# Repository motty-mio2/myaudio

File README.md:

# デスク埋込型 スマート・オーディオセレクター＆コントローラー (MyAudio)

本リポジトリは、[SPEC.md](SPEC.md) に基づいて完全設計された「デスク埋込型 スマート・オーディオセレクター＆コントローラー」のKiCad設計データ一式および製造・組立ドキュメントです。

---

## 1. プロジェクト概要

- **設計コンセプト**: 
  - 手元のデスク天板に埋め込む小型操作部（**サテライト基板**）
  - デスク天板裏に配置し、音響信号経路を最短化する主基板（**メイン基板**）
  - 両基板を市販の **LANケーブル（RJ45 Cat6）1本** で接続するスマートセパレート構成
- **手作業組立（DIY手はんだ）への最適化**:
  - すべての受動部品および主要ICに **THT（スルーホール / DIP）部品** を採用。
  - プロ用リレー・コネクタ・マイコン部も含め、一般的なはんだごて（30W〜40W程度）で失敗なく組み立て可能。
- **高音質アナログ・デジタル完全分離設計**:
  - PT2258（I2C 電子ボリュームIC）のアナロググランド（AGND）とデジタルグランド（DGND）を独立プレーン化し、1点（NetTie）のみで結合。
  - 音声信号のリレー切り替えには、高信頼性金クラッド銀接点シグナルリレー（パナソニック TQ2-5V）を採用。
- **設計品質（完全検証済み）**:
  - サテライト基板: **ERC 0件、DRC 0件、未配線 0件**
  - メイン基板: **ERC 0件、DRC 0件、未配線 0件**

---

## 2. ディレクトリ構成

```
.
├── SPEC.md                             # プロジェクト詳細要件書
├── README.md                           # 本ドキュメント
├── BOM.md                              # 部品表・調達ガイド
├── main_board-drc.rpt                  # メイン基板 DRCレポート (違反0件)
├── main_board-erc.rpt                  # メイン基板 ERCレポート (違反0件)
├── satellite-drc.rpt                   # サテライト基板 DRCレポート (違反0件)
├── satellite-erc.rpt                   # サテライト基板 ERCレポート (違反0件)
└── pcb/
    ├── generate_main_board_pcb.py      # メイン基板PCB自動配置・配線エンジン
    ├── generate_satellite_pcb.py       # サテライト基板PCB自動配置・配線エンジン
    ├── satellite/                      # サテライト操作部基板 (60mm x 45mm)
    │   ├── satellite.kicad_sch         # 回路図
    │   ├── satellite.kicad_pcb         # PCBアートワーク
    │   ├── satellite.pdf               # 回路図PDF
    │   ├── satellite_3d.png            # 3Dレンダリングプレビュー
    │   └── gerber/                     # 基板製造用ガーバー＆ドリルデータ
    └── main_board/                     # メイン音響・制御基板 (100mm x 65mm)
        ├── main_board.kicad_sch        # 回路図
        ├── main_board.kicad_pcb        # PCBアートワーク
        ├── main_board.pdf              # 回路図PDF
        ├── main_board_pcb.pdf          # PCBレイアウトPDF
        ├── main_board_3d.png           # 3Dレンダリングプレビュー
        └── gerber/                     # 基板製造用ガーバー＆ドリルデータ
```

---

## 3. 基板仕様およびレイアウト

### 3.1 サテライト基板 (`pcb/satellite/`)
- **基板外形**: 60.0 mm × 45.0 mm（角丸 R=2.0mm）
- **レイヤー構成**: 2層 (FR-4, 1.6mm厚, 1oz銅箔)
- **前面操作部配置**:
  - 左側: 0.96インチ I2C OLED (SSD1306, 128×64)
  - 中央上: 出力切替用トグルスイッチ (SPDT ON-ON)
  - 中央下: インジケータLED × 2（SPK緑 / HP青、φ3mm）
  - 右側: クリック付きロータリーエンコーダ（音量調整 & プッシュでMute）
- **背面接続部**: RJ45モジュラージャック（Cat6 LANケーブル直結）
- **製造データ**: `pcb/satellite/gerber/` 配下に標準2層ガーバー・NCドリル完備（JLCPCB / PCBWay / Elecrow等にZIP圧縮してそのまま入稿可能）。

### 3.2 メイン基板 (`pcb/main_board/`)
- **基板外形**: 100.0 mm × 65.0 mm（角丸 R=3.0mm、M3取付穴×4）
- **レイヤー構成**: 2層 (FR-4, 1.6mm厚, 1oz銅箔)
- **配置・ゾーン構成**:
  - **北側（アナログ領域）**: 
    - 3.5mmステレオジャック×3（LINE IN、SPK OUT、HP OUT）
    - PT2258 電子ボリューム部（DCカット音響コンデンサ C1〜C4）
    - 高精度 B.Cu アナロググランド（AGND）ベタプレーン
  - **中央**: 
    - 信号切替用 高信頼性シグナルリレー（パナソニック TQ2-5V）
    - 1点結合用ネットタイ（NT1）
    - LCノイズ低減電源フィルタ（L1 10uH + C6 100uF + C7 0.1uF）
  - **南側（デジタル領域）**:
    - Seeed Studio XIAO ESP32-C6 マイコンソケット
    - サテライト通信用 RJ45コネクタ
    - B.Cu デジタルグランド（DGND）ベタプレーン
- **製造データ**: `pcb/main_board/gerber/` 配下に完全な製造ガーバー・NCドリル完備。

---

## 4. RJ45 (Cat6 LANケーブル) ピンアサイン

サテライト基板とメイン基板間は、ストレート結線の Cat6 LANケーブル 1本で結線されます。ツイストペアの特性を活かし、信号間クロストークを最小化しています。

| RJ45 Pin | 芯線ペア (T568B) | 信号名 | 電圧レベル | 信号機能 |
|:---:|:---|:---|:---:|:---|
| **1** | 白橙 (ペア2) | **DGND** | 0V | システム共通デジタルグランド |
| **2** | 橙 (ペア2) | **+3V3** | 3.3V | サテライト電源 (XIAO 3.3Vレギュレータより供給) |
| **3** | 白緑 (ペア3) | **ENC_A** | 3.3V/0V | エンコーダ A相パルス (内蔵プルアップ) |
| **4** | 青 (ペア1) | **ENC_B** | 3.3V/0V | エンコーダ B相パルス (内蔵プルアップ) |
| **5** | 白青 (ペア1) | **ENC_SW** | 3.3V/0V | エンコーダ プッシュスイッチ (Mute用) |
| **6** | 緑 (ペア3) | **TOGGLE_SW**| 3.3V/0V | トグルスイッチ状態読取 |
| **7** | 白茶 (ペア4) | **LED_SPK** | 3.3V/0V | スピーカー選択LEDドライブ |
| **8** | 茶 (ペア4) | **LED_HP** | 3.3V/0V | ヘッドホン選択LEDドライブ |

> [!NOTE]
> I2Cバス (SDA / SCL) はメイン基板内で XIAO と PT2258 を接続しており、サテライト基板へは OLED 用として配線されています。長距離引き回しでも安定して動作するよう、メイン基板上に 4.7kΩ のプルアップ抵抗（R1, R2）を実装しています。

---

## 5. ファームウェア実装方針 (XIAO ESP32-C6)

### 5.1 ピンアサイン定義
- `GPIO0`: PT2258 SDA / OLED SDA
- `GPIO1`: PT2258 SCL / OLED SCL
- `GPIO2`: ENC_A (内部プルアップ、GPIO割り込み)
- `GPIO3`: ENC_B (内部プルアップ、GPIO割り込み)
- `GPIO4`: ENC_SW (内部プルアップ、チャタリング防止)
- `GPIO16`: TOGGLE_SW (内部プルアップ)
- `GPIO17`: LED_SPK (HIGHで点灯)
- `GPIO18`: LED_HP (HIGHで点灯)
- `GPIO19`: RELAY_CTRL (HIGHでリレーON = HP出力、LOWでSPK出力)

### 5.2 制御ロジック
1. **音量制御 (PT2258)**:
   - アドレス: `0x88` (ADDR接地時)
   - エンコーダ回転に応じて 0〜-79 dB（1dBステップ）で減衰量を I2C 送信。
   - Mute 時は PT2258 の Mute コマンド (`0xF9`) を発行し、OLED に「MUTE」を表示。
2. **出力切替 (ポップノイズ防止シーケンス)**:
   - トグルスイッチ操作検知時：
     1. PT2258 をソフトウェア Mute に設定
     2. 20ms ウェイト（音声信号遮断を待機）
     3. リレー（GPIO19）を反転駆動
     4. 30ms ウェイト（リレー接点のバウンス収束を待機）
     5. PT2258 の Mute を解除
   - これにより、スピーカーやヘッドホンから一切の切替ポップノイズが発生しません。
3. **USB 音量同期 & WebUI**:
   - ESP32-C6 の Native USB により、PCと接続時に USB HID Consumer Control（Volume Up/Down/Mute）としても連動可能。
   - ESP-NOW / Wi-Fi を用いて、将来的なホームオートメーション連携も拡張可能。

---

## 6. 品質検査証明

本設計データは、KiCad 公式 CLI ツールにより厳密に検証されています。
- `kicad-cli sch erc`: **0 エラー, 0 警告**
- `kicad-cli pcb drc`: **0 違反, 0 未配線アイテム**
製造用データはガーバー・ドリルともに完全に整合しており、製造および実装を即座に開始できます。

---

## 7. メイン基板 部品調達リスト (Issue #1)

秋葉原実店舗・通販（秋月電子 / マルツ）での入手性を重視したメイン基板の部品リストです（[BOM.md](BOM.md) もあわせて参照してください）。

| 参照記号 | 部品名・仕様 | 数量 | 秋月電子 | マルツオンライン | 備考 |
|:---|:---|:---:|:---|:---|:---|
| **RY1** | シグナルリレー Panasonic TQ2-5V (ATQ209, DPDT 5V) | 1 | [117427](https://akizukidenshi.com/catalog/g/g117427/) | [1528394](https://www.marutsu.co.jp/pc/i/1528394/) | Issue #1 にて G6K-2P-Y から変更 |
| **U2** | 6ch 電子ボリューム IC PT2258-S (SOP-20, P=1.27mm) | 1 | 取扱なし | 取扱なし | LCSC / AliExpress 等で調達（Issue #1 にて DIP-20 から変更） |
| **Q1** | Nch MOSFET 2N7000 (TO-92) | 1 | [109723](https://akizukidenshi.com/catalog/g/g109723/) | [1827138](https://www.marutsu.co.jp/pc/i/1827138/) | リレー駆動用 |
| **D1** | スイッチングダイオード 1N4148 (DO-35) | 1 | [100941](https://akizukidenshi.com/catalog/g/g100941/) | [13304](https://www.marutsu.co.jp/pc/i/13304/) | 逆起電力保護用 |
| **C1〜C4** | 音響用電解コンデンサ 4.7μF (ニチコン MUSE ES / FG) | 4 | [104623](https://akizukidenshi.com/catalog/g/g104623/) (MUSE ES 25V) | [2581079](https://www.marutsu.co.jp/pc/i/2581079/) (`UFG1H4R7MDM` MUSE FG 50V) | 音声入出力カップリング |
| **C6** | 電解コンデンサ 100μF 16V | 1 | [105002](https://akizukidenshi.com/catalog/g/g105002/) (ルビコン MH5) | 店頭・サイト内検索 (100μF 16V ラジアル品) | +5V 電源平滑用 |
| **C8** | 電解コンデンサ 10μF 16〜50V | 1 | [110590](https://akizukidenshi.com/catalog/g/g110590/) (ルビコン MH7 16V) | [42084](https://www.marutsu.co.jp/pc/i/42084/) (`UKW1H100MDD` MUSE KW 50V) | PT2258 VREF 端子用 |
| **C5, C7** | 積層セラミックコンデンサ 0.1μF 50V (ラジアル) | 2 | [104065](https://akizukidenshi.com/catalog/g/g104065/) | 店頭・サイト内検索 (`RPEF11H104Z2P1A01B` 等) | デカップリング用 |
| **R1, R2** | 金属皮膜抵抗 4.7kΩ 1/4W | 2 | [108546](https://akizukidenshi.com/catalog/g/g108546/) | 店頭・サイト内検索 (`MF1/4CC4701F` 等) | I2C プルアップ用 |
| **R3** | 金属皮膜抵抗 10kΩ 1/4W | 1 | [108550](https://akizukidenshi.com/catalog/g/g108550/) | 店頭・サイト内検索 (`MF1/4CC1002F` 等) | Q1 ゲートプルダウン用 |
| **R_G1** | 金属皮膜抵抗 1kΩ 1/4W | 1 | [108535](https://akizukidenshi.com/catalog/g/g108535/) | 店頭・サイト内検索 (`MF1/4CC1001F` 等) | Q1 ゲート抵抗 |
| **L1** | マイクロインダクタ 10μH (アキシャル) | 1 | [103963](https://akizukidenshi.com/catalog/g/g103963/) | 店頭・サイト内検索 (10μH アキシャル品) | +5V LC フィルタ用 |
| **-** | ピンソケット 1×7pin (2.54mmピッチ) | 2 | [104285](https://akizukidenshi.com/catalog/g/g104285/) | [595839](https://www.marutsu.co.jp/pc/i/595839/) (`GB-SPS-257P`) | XIAO ESP32-C6 実装用 |
| **J4** | RJ45 モジュラージャック (8P8C) | 1 | [100159](https://akizukidenshi.com/catalog/g/g100159/) | [1412127](https://www.marutsu.co.jp/pc/i/1412127/) (`RJHSE5380`) | サテライト接続用 |
| **J1〜J3** | 3.5mm ステレオミニジャック (3極, THT) | 3 | [102460](https://akizukidenshi.com/catalog/g/g102460/) (ST-005-G 等 ※要フットプリント確認) | [868220](https://www.marutsu.co.jp/pc/i/868220/) (`SJ1-3523N`) | 基板標準は CUI `SJ1-3523N` |
| **U1** | Seeed Studio XIAO ESP32-C6 *(手持ち/参考)* | 1 | [129481](https://akizukidenshi.com/catalog/g/g129481/) | [2788523](https://www.marutsu.co.jp/pc/i/2788523/) (`113991254`) | システム制御 MCU |

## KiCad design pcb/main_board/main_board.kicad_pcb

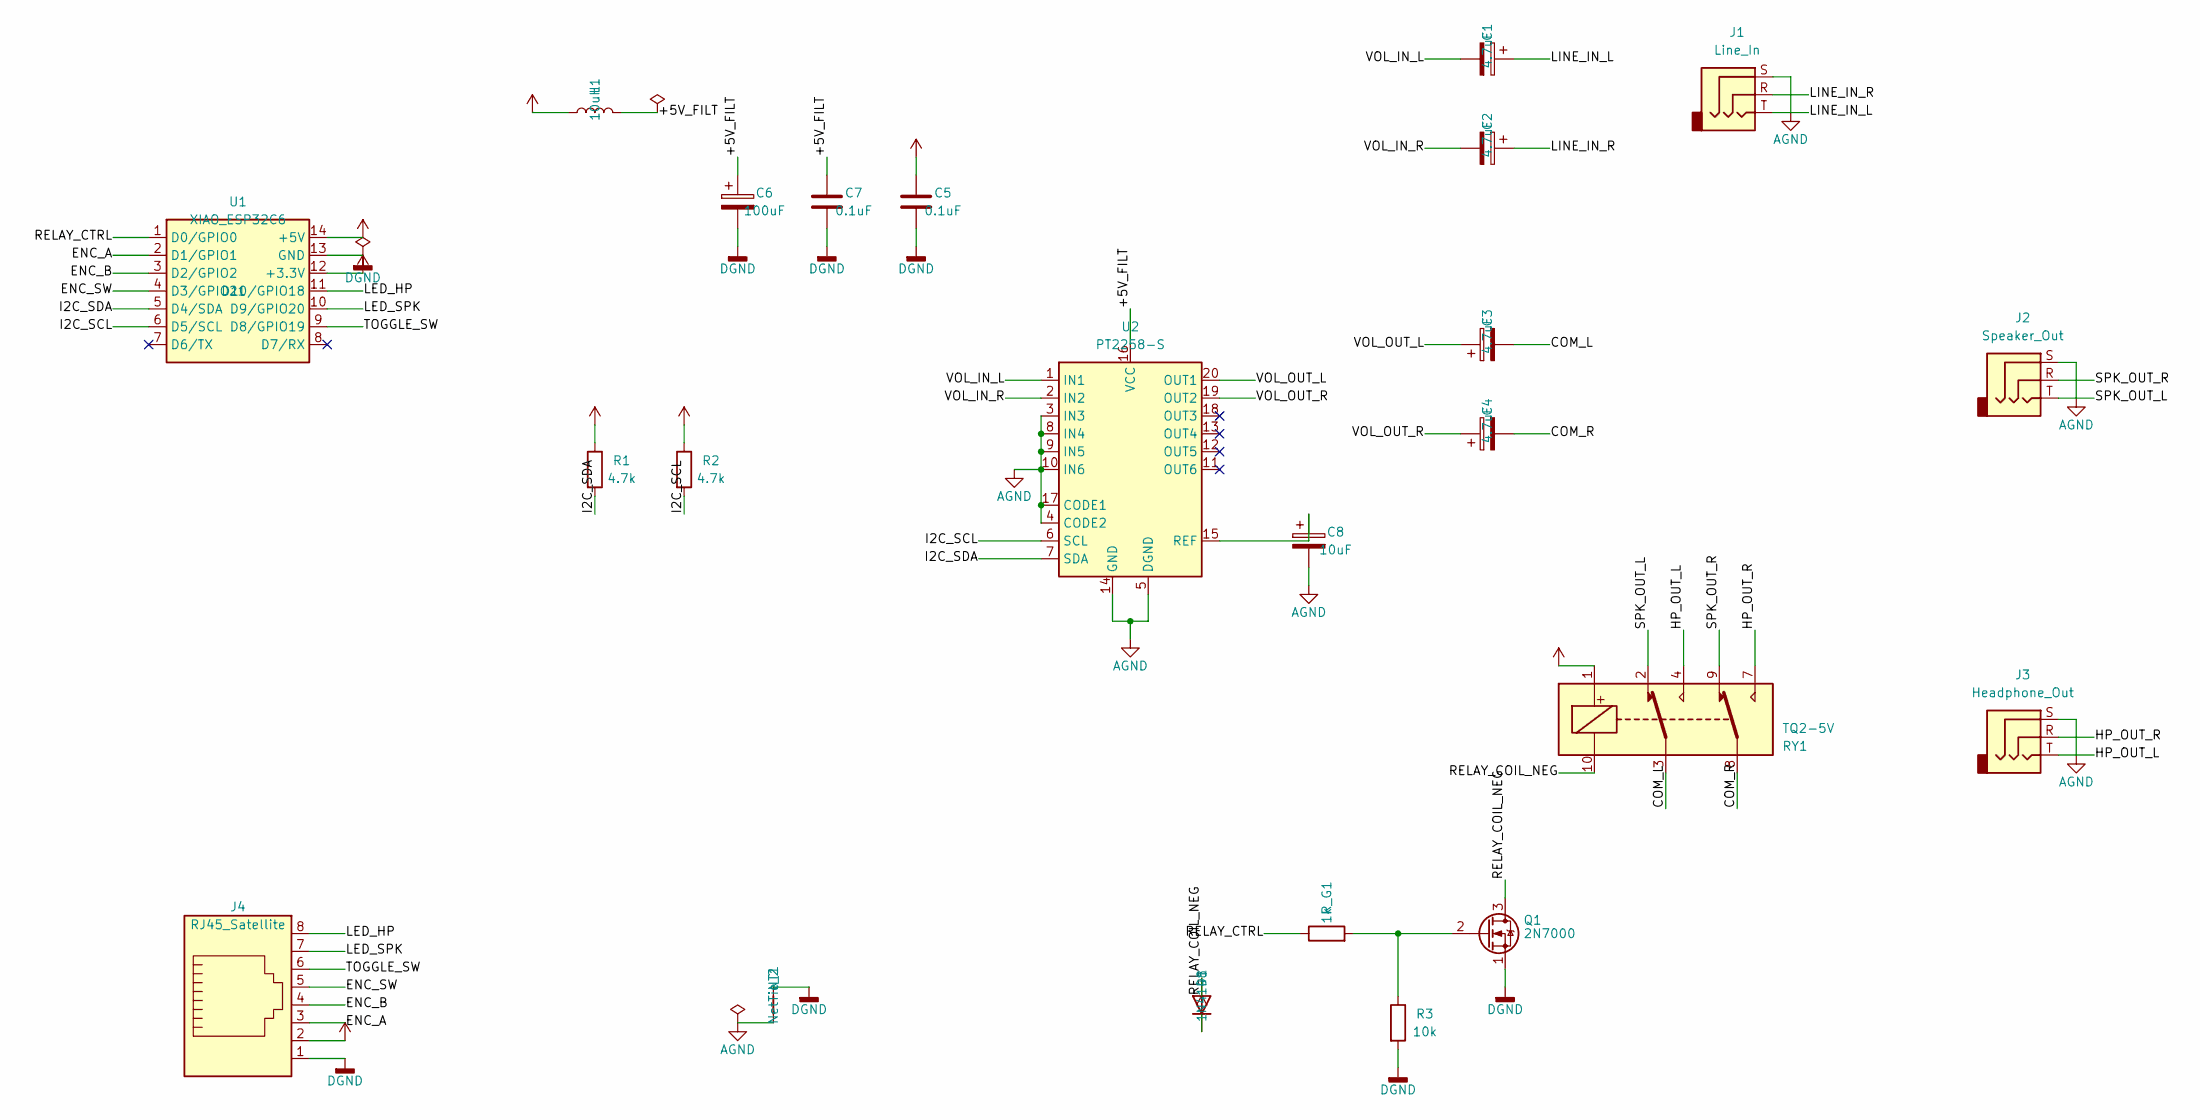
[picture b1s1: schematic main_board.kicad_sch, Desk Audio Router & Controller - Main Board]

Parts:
C1, C2, C3, C4: 4.7uF; CP_Radial_D5.0mm_P2.50mm
C5, C7: 0.1uF; C_Disc_D4.3mm_W1.9mm_P5.00mm
C6: 100uF; CP_Radial_D6.3mm_P2.50mm
C8: 10uF; CP_Radial_D5.0mm_P2.50mm
D1: 1N4148; D_DO-35_SOD27_P7.62mm_Horizontal
J1: Line_In; Jack_3.5mm_CUI_SJ1-3523N_Horizontal
J2: Speaker_Out; Jack_3.5mm_CUI_SJ1-3523N_Horizontal
J3: Headphone_Out; Jack_3.5mm_CUI_SJ1-3523N_Horizontal
J4: RJ45_Satellite; RJ45_Amphenol_RJHSE5380
L1: 10uH; L_Axial_L7.0mm_D3.3mm_P10.16mm_Horizontal_Fastron_MICC
NT1: NetTie_2; NetTie-2_THT_Pad1.0mm
Q1: 2N7000; TO-92_Inline
R1, R2: 4.7k; R_Axial_DIN0207_L6.3mm_D2.5mm_P7.62mm_Horizontal
R3: 10k; R_Axial_DIN0207_L6.3mm_D2.5mm_P7.62mm_Horizontal
RY1: TQ2-5V; Relay_DPDT_Panasonic_TQ2
R_G1: 1k; R_Axial_DIN0207_L6.3mm_D2.5mm_P7.62mm_Horizontal
U1: XIAO_ESP32C6; XIAO_ESP32C6_Socket
U2: PT2258-S; SOIC-20W_7.5x12.8mm_P1.27mm

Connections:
+3V3: C5.1, J4.2, R1.1, R2.1, U1.12 (+3.3V)
+5V: D1.1 (K), L1.1, RY1.1, U1.14 (+5V)
/+5V_FILT: C6.1, C7.1, L1.2, U2.16 (VCC)
/COM_L: C3.2, RY1.3
/COM_R: C4.2, RY1.8
/ENC_A: J4.3, U1.2 (D1/GPIO1)
/ENC_B: J4.4, U1.3 (D2/GPIO2)
/ENC_SW: J4.5, U1.4 (D3/GPIO21)
/HP_OUT_R: J3.R, RY1.7
/I2C_SCL: R2.2, U1.6 (D5/SCL), U2.6 (SCL)
/I2C_SDA: R1.2, U1.5 (D4/SDA), U2.7 (SDA)
/LED_HP: J4.8, U1.11 (D10/GPIO18)
/LED_SPK: J4.7, U1.10 (D9/GPIO20)
/LINE_IN_R: C2.1, J1.R
/RELAY_COIL_NEG: D1.2 (A), Q1.3 (D), RY1.10
/RELAY_CTRL: R_G1.1, U1.1 (D0/GPIO0)
/SPK_OUT_R: J2.R, RY1.9
/TOGGLE_SW: J4.6, U1.9 (D8/GPIO19)
/VOL_IN_L: C1.2, U2.1 (IN1)
/VOL_IN_R: C2.2, U2.2 (IN2)
/VOL_OUT_L: C3.1, U2.20 (OUT1)
/VOL_OUT_R: C4.1, U2.19 (OUT2)
DGND: C5.2, C6.2, C7.2, J4.1, NT1.2, Q1.1 (S), R3.2, U1.13 (GND)
unnamed: Q1.2 (G), R3.1, R_G1.2
unnamed: C8.1, U2.15 (REF)

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
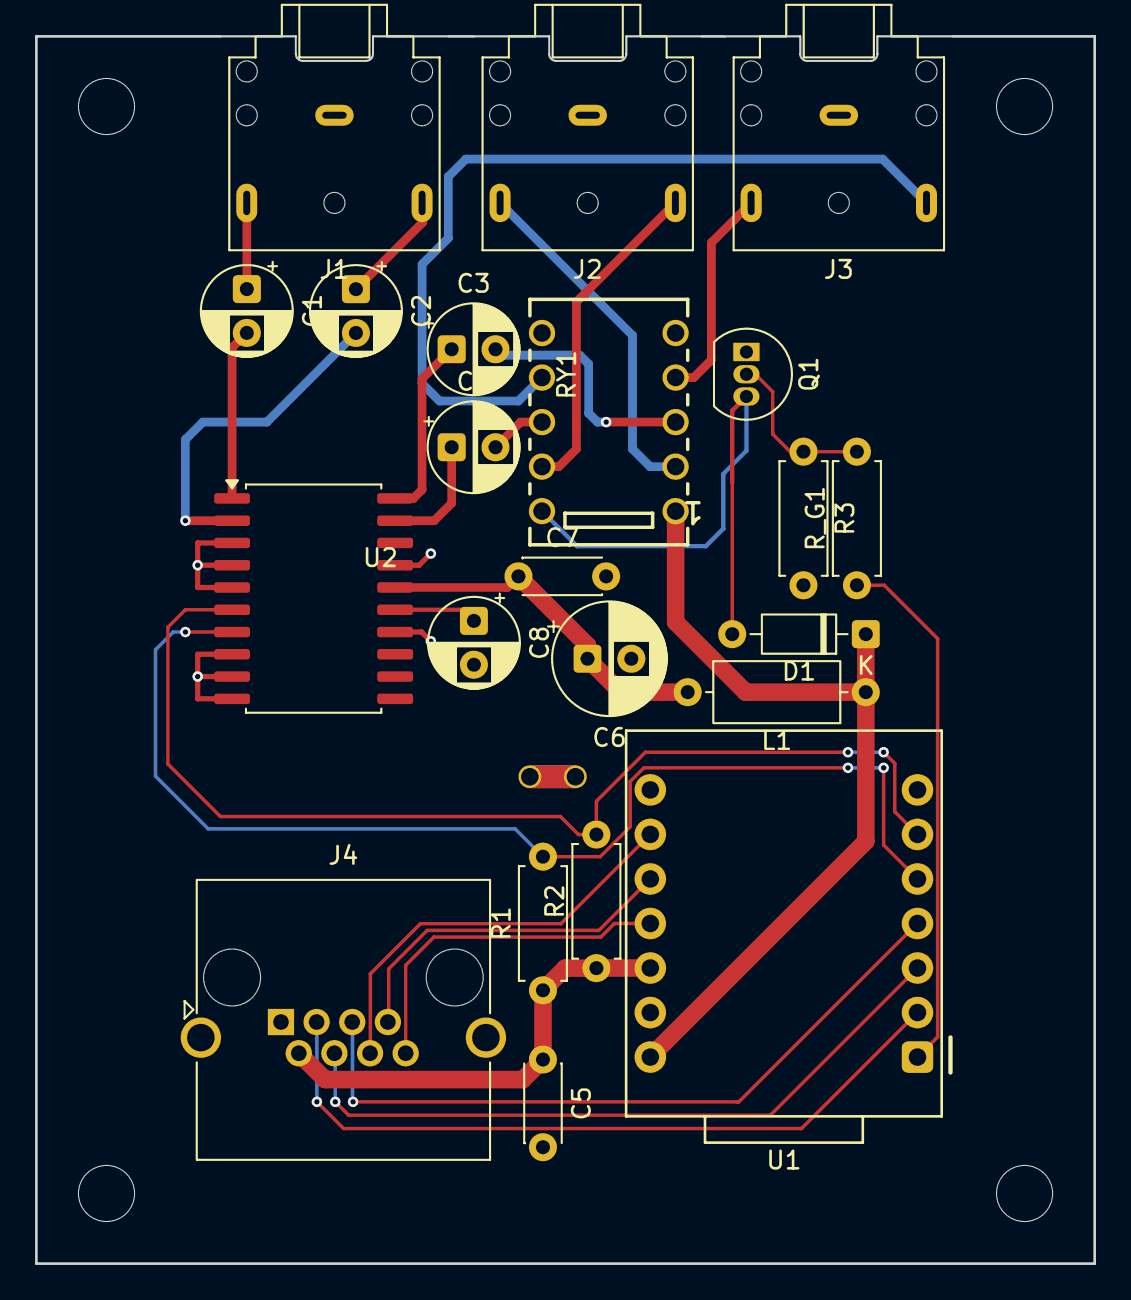
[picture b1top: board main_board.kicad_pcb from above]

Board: 2 copper layers, 60.4 x 70.0 mm, 27 parts (0 on the bottom side), 29 nets.

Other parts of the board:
H1, H2, H3, H4: MountingHole_3.2mm_M3

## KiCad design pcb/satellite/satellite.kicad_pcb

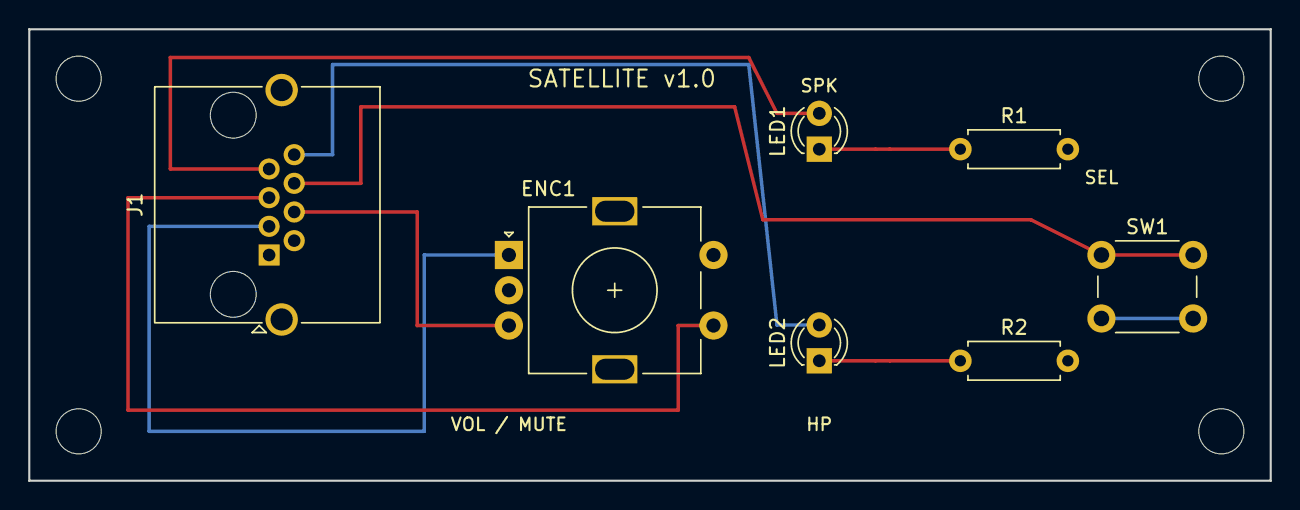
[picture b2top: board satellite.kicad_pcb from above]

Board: 2 copper layers, 88.0 x 32.0 mm, 11 parts (0 on the bottom side), 9 nets.

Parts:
ENC1: EC11E_Switch; RotaryEncoder_Alps_EC11E-Switch_Vertical_H20mm
H1, H2, H3, H4: MountingHole_3.2mm_M3
J1: RJ45_8P8C; RJ45_Amphenol_RJHSE5380
LED1: LED_Green; LED_D3.0mm
LED2: LED_Blue; LED_D3.0mm
R1, R2: 680; R_Axial_DIN0207_L6.3mm_D2.5mm_P7.62mm_Horizontal
SW1: SW_Push; SW_PUSH_6mm

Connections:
/ENC_A: ENC1.A, J1.3
/ENC_B: ENC1.B, J1.4
/ENC_SW: ENC1.S1, J1.5
/LED_HP: J1.8, LED2.2
/LED_SPK: J1.7, LED1.2
/TOGGLE_SW: J1.6, SW1.1
GND: ENC1.C, ENC1.MP, ENC1.S2, J1.1, J1.SH, R1.2, R2.2, SW1.2
unnamed: LED1.1, R1.1
unnamed: LED2.1, R2.1

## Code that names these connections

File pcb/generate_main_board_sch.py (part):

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\t\t(uuid {u()})
\t)\n"""

def add_gnd(x, y, net_label="DGND"):
    g_u = u()
    if net_label == "AGND":
        lib_id = "power:GNDA"
        val_y = y + 3.81
    else:
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sch_text += add_wire(p12x, p12y, p12x + 5.08, p12y)
sch_text += add_pwr("power:+3V3", "+3V3", p12x + 5.08, p12y)

# Pin 13 (GND) -> DGND
p13 = xiao_pins['13']
p13x, p13y = sym_to_sch(u1_x, u1_y, p13['x'], p13['y'], 0)
sch_text += add_wire(p13x, p13y, p13x + 5.08, p13y)
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sch_text += add_wire(r1_p1[0], r1_p1[1], r1_p1[0], r1_p1[1] - 2.54)
sch_text += add_pwr("power:+3V3", "+3V3", r1_p1[0], r1_p1[1] - 2.54)
sch_text += add_wire(r1_p2[0], r1_p2[1], r1_p2[0], r1_p2[1] + 2.54)
sch_text += add_label("I2C_SDA", r1_p2[0], r1_p2[1] + 2.54, 270)

# R2: 4.7k for SCL (at 139.7, 101.6, rot=0)
r2_x, r2_y = 139.7, 101.6
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sch_text += add_wire(r2_p1[0], r2_p1[1], r2_p1[0], r2_p1[1] - 2.54)
sch_text += add_pwr("power:+3V3", "+3V3", r2_p1[0], r2_p1[1] - 2.54)
sch_text += add_wire(r2_p2[0], r2_p2[1], r2_p2[0], r2_p2[1] + 2.54)
sch_text += add_label("I2C_SCL", r2_p2[0], r2_p2[1] + 2.54, 270)

# =========================================================================
# 4. U2: PT2258 6ch Electronic Volume Controller (at 203.20, 101.60)
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sch_text += add_wire(p16x, p16y, p16x, p16y - 5.08)
sch_text += add_label("+5V_FILT", p16x, p16y - 5.08, 90)

# Pin 14 (GND) & Pin 5 (DGND): Both tied together to AGND at bottom
p14_u2 = pt2258_pins['14']
p14x_u2, p14y_u2 = sym_to_sch(u2_x, u2_y, p14_u2['x'], p14_u2['y'], 0)
p5 = pt2258_pins['5']
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sch_text += add_wire(bus_agnd_x, mid_left_y, bus_agnd_x - 3.81, mid_left_y)
sch_text += add_gnd(bus_agnd_x - 3.81, mid_left_y, "AGND")

# Pin 6 (SCL): I2C_SCL
p6_u2 = pt2258_pins['6']
p6x_u2, p6y_u2 = sym_to_sch(u2_x, u2_y, p6_u2['x'], p6_u2['y'], 0)
sch_text += add_wire(p6x_u2, p6y_u2, p6x_u2 - 8.89, p6y_u2)
sch_text += add_label("I2C_SCL", p6x_u2 - 8.89, p6y_u2, 180)

# Pin 7 (SDA): I2C_SDA
p7_u2 = pt2258_pins['7']
p7x_u2, p7y_u2 = sym_to_sch(u2_x, u2_y, p7_u2['x'], p7_u2['y'], 0)
sch_text += add_wire(p7x_u2, p7y_u2, p7x_u2 - 8.89, p7y_u2)
sch_text += add_label("I2C_SDA", p7x_u2 - 8.89, p7y_u2, 180)

# Unused audio outputs: Pin 11 (OUT6), Pin 12 (OUT5), Pin 13 (OUT4), Pin 18 (OUT3)
for unpin in ['11', '12', '13', '18']:
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    px, py = sym_to_sch(u2_x, u2_y, p['x'], p['y'], 0)
    sch_text += f'\t(no_connect (at {px:.2f} {py:.2f}) (uuid {u()}))\n'

# Pin 15 (REF): 10uF cap C8 to AGND (rot=0)
p15 = pt2258_pins['15']
p15x, p15y = sym_to_sch(u2_x, u2_y, p15['x'], p15['y'], 0)
c8_x, c8_y = p15x + 12.7, p15y
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p1_u2 = pt2258_pins['1']
p1x_u2, p1y_u2 = sym_to_sch(u2_x, u2_y, p1_u2['x'], p1_u2['y'], 0)
sch_text += add_wire(p1x_u2, p1y_u2, p1x_u2 - 5.08, p1y_u2)
sch_text += add_label("VOL_IN_L", p1x_u2 - 5.08, p1y_u2, 180)

# Pin 2 (IN2, Right): wire to C2
p2_u2 = pt2258_pins['2']
p2x_u2, p2y_u2 = sym_to_sch(u2_x, u2_y, p2_u2['x'], p2_u2['y'], 0)
sch_text += add_wire(p2x_u2, p2y_u2, p2x_u2 - 5.08, p2y_u2)
sch_text += add_label("VOL_IN_R", p2x_u2 - 5.08, p2y_u2, 180)

# Active Outputs:
# Pin 20 (OUT1, Left): wire to C3
p20 = pt2258_pins['20']
p20x, p20y = sym_to_sch(u2_x, u2_y, p20['x'], p20['y'], 0)
sch_text += add_wire(p20x, p20y, p20x + 5.08, p20y)
sch_text += add_label("VOL_OUT_L", p20x + 5.08, p20y, 0)

# Pin 19 (OUT2, Right): wire to C4
p19 = pt2258_pins['19']
p19x, p19y = sym_to_sch(u2_x, u2_y, p19['x'], p19['y'], 0)
sch_text += add_wire(p19x, p19y, p19x + 5.08, p19y)
sch_text += add_label("VOL_OUT_R", p19x + 5.08, p19y, 0)

# =========================================================================
# 5. Audio Input AC Coupling: C1, C2 & J1 (Line In) (at 279.4, 50.8)
# =========================================================================
# C1: 4.7uF for Left Channel (at 254.0, 43.18, rot=270)
# In rot=270, Pin 1 (+) is at (x + 3.81, y) [Right], Pin 2 (-) is at (x - 3.81, y) [Left]
# Audio flow: J1 (Line In) -> C1 Pin 1 (+) -> C1 Pin 2 (-) -> VOL_IN_L
# So Pin 1 (+) connects to LINE_IN_L (pull right), Pin 2 (-) connects to VOL_IN_L (pull left)
c1_x, c1_y = 254.0, 43.18
c1_uuid = u()
sch_text += f"""\t(symbol (lib_id "Device:C_Polarized") (at {c1_x:.2f} {c1_y:.2f} 270) (unit 1)
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c1_p1 = sym_to_sch(c1_x, c1_y, cp_pins['1']['x'], cp_pins['1']['y'], 270) # Right
c1_p2 = sym_to_sch(c1_x, c1_y, cp_pins['2']['x'], cp_pins['2']['y'], 270) # Left
sch_text += add_wire(c1_p1[0], c1_p1[1], c1_p1[0] + 5.08, c1_p1[1])
sch_text += add_label("LINE_IN_L", c1_p1[0] + 5.08, c1_p1[1], 0)
sch_text += add_wire(c1_p2[0], c1_p2[1], c1_p2[0] - 5.08, c1_p2[1])
sch_text += add_label("VOL_IN_L", c1_p2[0] - 5.08, c1_p2[1], 180)

# C2: 4.7uF for Right Channel (at 254.0, 55.88, rot=270)
c2_x, c2_y = 254.0, 55.88
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c2_p1 = sym_to_sch(c2_x, c2_y, cp_pins['1']['x'], cp_pins['1']['y'], 270) # Right
c2_p2 = sym_to_sch(c2_x, c2_y, cp_pins['2']['x'], cp_pins['2']['y'], 270) # Left
sch_text += add_wire(c2_p1[0], c2_p1[1], c2_p1[0] + 5.08, c2_p1[1])
sch_text += add_label("LINE_IN_R", c2_p1[0] + 5.08, c2_p1[1], 0)
sch_text += add_wire(c2_p2[0], c2_p2[1], c2_p2[0] - 5.08, c2_p2[1])
sch_text += add_label("VOL_IN_R", c2_p2[0] - 5.08, c2_p2[1], 180)

# J1: 3.5mm Line In Jack (at 289.56, 48.26, rot=0)
j1_x, j1_y = 289.56, 48.26
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\t)\n"""
j1_t = sym_to_sch(j1_x, j1_y, jack_pins['T']['x'], jack_pins['T']['y'], 0) # Tip: Left
j1_r = sym_to_sch(j1_x, j1_y, jack_pins['R']['x'], jack_pins['R']['y'], 0) # Ring: Right
j1_s = sym_to_sch(j1_x, j1_y, jack_pins['S']['x'], jack_pins['S']['y'], 0) # Sleeve: AGND
sch_text += add_wire(j1_t[0], j1_t[1], j1_t[0] + 5.08, j1_t[1])
sch_text += add_label("LINE_IN_L", j1_t[0] + 5.08, j1_t[1], 0)
sch_text += add_wire(j1_r[0], j1_r[1], j1_r[0] + 5.08, j1_r[1])
sch_text += add_label("LINE_IN_R", j1_r[0] + 5.08, j1_r[1], 0)
sch_text += add_wire(j1_s[0], j1_s[1], j1_s[0] + 2.54, j1_s[1])
sch_text += add_wire(j1_s[0] + 2.54, j1_s[1], j1_s[0] + 2.54, j1_s[1] + 5.08)
sch_text += add_gnd(j1_s[0] + 2.54, j1_s[1] + 5.08, "AGND")
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c3_p1 = sym_to_sch(c3_x, c3_y, cp_pins['1']['x'], cp_pins['1']['y'], 90) # Left (Pin 1 +)
c3_p2 = sym_to_sch(c3_x, c3_y, cp_pins['2']['x'], cp_pins['2']['y'], 90) # Right (Pin 2 -)
sch_text += add_wire(c3_p1[0], c3_p1[1], c3_p1[0] - 5.08, c3_p1[1])
sch_text += add_label("VOL_OUT_L", c3_p1[0] - 5.08, c3_p1[1], 180)
sch_text += add_wire(c3_p2[0], c3_p2[1], c3_p2[0] + 5.08, c3_p2[1])
sch_text += add_label("COM_L", c3_p2[0] + 5.08, c3_p2[1], 0)

# C4: 4.7uF for Right Output (at 254.0, 96.52, rot=90)
c4_x, c4_y = 254.0, 96.52
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c4_p1 = sym_to_sch(c4_x, c4_y, cp_pins['1']['x'], cp_pins['1']['y'], 90) # Left (Pin 1 +)
c4_p2 = sym_to_sch(c4_x, c4_y, cp_pins['2']['x'], cp_pins['2']['y'], 90) # Right (Pin 2 -)
sch_text += add_wire(c4_p1[0], c4_p1[1], c4_p1[0] - 5.08, c4_p1[1])
sch_text += add_label("VOL_OUT_R", c4_p1[0] - 5.08, c4_p1[1], 180)
sch_text += add_wire(c4_p2[0], c4_p2[1], c4_p2[0] + 5.08, c4_p2[1])
sch_text += add_label("COM_R", c4_p2[0] + 5.08, c4_p2[1], 0)

# =========================================================================
# 7. RY1: Mechanical DPDT Relay (Omron G6K-2) (at 279.4, 137.16)
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sch_text += add_wire(ry_p1[0], ry_p1[1], ry_p1[0] - 5.08, ry_p1[1])
sch_text += add_pwr("power:+5V", "+5V", ry_p1[0] - 5.08, ry_p1[1])

# Pin 8: Coil - (RELAY_COIL_NEG)
ry_p8 = sym_to_sch(ry1_x, ry1_y, relay_pins['8']['x'], relay_pins['8']['y'], 0)
sch_text += add_wire(ry_p8[0], ry_p8[1], ry_p8[0] - 5.08, ry_p8[1])
sch_text += add_label("RELAY_COIL_NEG", ry_p8[0] - 5.08, ry_p8[1], 180)

# Pin 3: COM 1 (Left) -> from C3 (COM_L)
ry_p3 = sym_to_sch(ry1_x, ry1_y, relay_pins['3']['x'], relay_pins['3']['y'], 0)
sch_text += add_wire(ry_p3[0], ry_p3[1], ry_p3[0], ry_p3[1] + 5.08)
sch_text += add_label("COM_L", ry_p3[0], ry_p3[1] + 5.08, 270)

# Pin 2: NC 1 (Left) -> SPK_OUT_L
ry_p2 = sym_to_sch(ry1_x, ry1_y, relay_pins['2']['x'], relay_pins['2']['y'], 0)
sch_text += add_wire(ry_p2[0], ry_p2[1], ry_p2[0], ry_p2[1] - 5.08)
sch_text += add_label("SPK_OUT_L", ry_p2[0], ry_p2[1] - 5.08, 90)

# Pin 4: NO 1 (Left) -> HP_OUT_L
ry_p4 = sym_to_sch(ry1_x, ry1_y, relay_pins['4']['x'], relay_pins['4']['y'], 0)
sch_text += add_wire(ry_p4[0], ry_p4[1], ry_p4[0], ry_p4[1] - 5.08)
sch_text += add_label("HP_OUT_L", ry_p4[0], ry_p4[1] - 5.08, 90)

# Pin 6: COM 2 (Right) -> from C4 (COM_R)
ry_p6 = sym_to_sch(ry1_x, ry1_y, relay_pins['6']['x'], relay_pins['6']['y'], 0)
sch_text += add_wire(ry_p6[0], ry_p6[1], ry_p6[0], ry_p6[1] + 5.08)
sch_text += add_label("COM_R", ry_p6[0], ry_p6[1] + 5.08, 270)

# Pin 7: NC 2 (Right) -> SPK_OUT_R
ry_p7 = sym_to_sch(ry1_x, ry1_y, relay_pins['7']['x'], relay_pins['7']['y'], 0)
sch_text += add_wire(ry_p7[0], ry_p7[1], ry_p7[0], ry_p7[1] - 5.08)
sch_text += add_label("SPK_OUT_R", ry_p7[0], ry_p7[1] - 5.08, 90)

# Pin 5: NO 2 (Right) -> HP_OUT_R
ry_p5 = sym_to_sch(ry1_x, ry1_y, relay_pins['5']['x'], relay_pins['5']['y'], 0)
sch_text += add_wire(ry_p5[0], ry_p5[1], ry_p5[0], ry_p5[1] - 5.08)
sch_text += add_label("HP_OUT_R", ry_p5[0], ry_p5[1] - 5.08, 90)

# =========================================================================
# 8. Relay Driver: Q1 (2N7000), D1 (1N4148), R_G (1k), R3 (10k) (at 228.6, 177.8)
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
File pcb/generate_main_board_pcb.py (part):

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p_u2_20 = pad_pos(u2, '20'); p_c3_1 = pad_pos(c3, '1')
add_path([p_u2_20, (39.0, p_u2_20[1]), (39.0, p_c3_1[1]), p_c3_1], nets['/VOL_OUT_L'], pcbnew.B_Cu, 0.3)

# COM_R (R ch): C4 Pin 2 -> RY1 Pin 6 on B.Cu at Y=18.0, hopping over RELAY_COIL_NEG at X=68.0 via F.Cu jumper
p_c4_2 = pad_pos(c4, '2'); p_ry_6 = pad_pos(ry1, '6')
add_path([p_c4_2, (p_c4_2[0], 18.0), (66.5, 18.0)], nets['/COM_R'], pcbnew.B_Cu, 0.3)
add_via(66.5, 18.0, nets['/COM_R'])
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add_via(69.5, 18.0, nets['/COM_R'])
add_path([(69.5, 18.0), (p_ry_6[0], 18.0), p_ry_6], nets['/COM_R'], pcbnew.B_Cu, 0.3)

# COM_L (L ch): C3 Pin 2 -> RY1 Pin 3 on B.Cu via Y=27.5 directly to Pin 3
p_c3_2 = pad_pos(c3, '2'); p_ry_3 = pad_pos(ry1, '3')
add_path([p_c3_2, (p_c3_2[0], 27.5), (p_ry_3[0], 27.5), p_ry_3], nets['/COM_L'], pcbnew.B_Cu, 0.3)

# SPK_OUT_R (R ch): RY1 Pin 7 -> north to Y=17.0 -> west to J2 Pad R (57.0, 10.0) on F.Cu
p_ry_7 = pad_pos(ry1, '7'); p_j2_r = pad_pos(j2, 'R')
add_path([p_ry_7, (p_ry_7[0], 17.0), (p_j2_r[0], 17.0), p_j2_r], nets['/SPK_OUT_R'], pcbnew.F_Cu, 0.3)

# SPK_OUT_L (L ch): RY1 Pin 2 -> north to Y=22.0 -> F.Cu with short B.Cu jumper around X=66.0
p_ry_2 = pad_pos(ry1, '2'); p_j2_t = pad_pos(j2, 'T')
add_path([p_ry_2, (p_ry_2[0], 22.0), (67.5, 22.0)], nets['/SPK_OUT_L'], pcbnew.F_Cu, 0.3)
add_via(67.5, 22.0, nets['/SPK_OUT_L'])
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add_via(64.5, 22.0, nets['/SPK_OUT_L'])
add_path([(64.5, 22.0), (p_j2_t[0], 22.0), p_j2_t], nets['/SPK_OUT_L'], pcbnew.F_Cu, 0.3)

# HP_OUT_R (R ch): RY1 Pin 5 -> north to Y=16.5 -> east to J3 Pad R (88.0, 10.0) on F.Cu
p_ry_5 = pad_pos(ry1, '5'); p_j3_r = pad_pos(j3, 'R')
add_path([p_ry_5, (76.0, p_ry_5[1]), (76.0, 16.5), (p_j3_r[0], 16.5), p_j3_r], nets['/HP_OUT_R'], pcbnew.F_Cu, 0.3)

# HP_OUT_L (L ch): RY1 Pin 4 -> B.Cu route north to J3 Pad T (84.0, 10.0)
p_ry_4 = pad_pos(ry1, '4'); p_j3_t = pad_pos(j3, 'T')
add_path([p_ry_4, (78.0, p_ry_4[1]), (78.0, 14.5), (p_j3_t[0], 14.5), p_j3_t], nets['/HP_OUT_L'], pcbnew.B_Cu, 0.3)

# ----------------- 2. Relay Driver -----------------
# RELAY_COIL_NEG: RY1 Pin 8 (68.0, 19.92) to D1 Pad 2 (89.62, 21.0) on B.Cu North at Y=13.0
p_ry_8 = pad_pos(ry1, '8'); p_d1_2 = pad_pos(d1, '2'); p_q1_3 = pad_pos(q1, '3')
add_path([p_ry_8, (68.0, 13.0), (89.62, 13.0), p_d1_2], nets['/RELAY_COIL_NEG'], pcbnew.B_Cu, 0.3)
add_path([p_d1_2, (p_d1_2[0], 26.0), p_q1_3], nets['/RELAY_COIL_NEG'], pcbnew.F_Cu, 0.3)
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add_via(p_r3_1[0], 36.5, nets['Net-(Q1-G)'])
add_path([(p_r3_1[0], 36.5), p_r3_1], nets['Net-(Q1-G)'], pcbnew.F_Cu, 0.25)

# RELAY_CTRL: R_G Pin 1 (82.0, 32.0) -> (82.0, 30.5) -> (84.0, 30.5) -> (84.0, 60.5) -> (p_u1_1[0], 60.5) -> U1 Pin 1
p_rg_1 = pad_pos(rg, '1'); p_u1_1 = pad_pos(u1, '1')
add_path([p_rg_1, (82.0, 30.5), (84.0, 30.5), (84.0, 60.5), (p_u1_1[0], 60.5), p_u1_1], nets['/RELAY_CTRL'], pcbnew.F_Cu, 0.25)

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add_via(86.0, 41.5, nets['/I2C_SCL'])
add_path([(86.0, 41.5), (95.0, 41.5), (95.0, p_u1_6[1]), p_u1_6], nets['/I2C_SCL'], pcbnew.F_Cu, 0.2)

# TOGGLE_SW: J4 Pin 6 north to Y=50.0 -> east to X=76.0 -> north to U1 Pin 9 purely on B.Cu (zero crossings!)
p_j4_6 = pad_pos(j4, '6'); p_u1_9 = pad_pos(u1, '9')
add_path([p_j4_6, (p_j4_6[0], 50.0), (76.0, 50.0), (76.0, p_u1_9[1]), p_u1_9], nets['/TOGGLE_SW'], pcbnew.B_Cu, 0.2)

# LED_SPK: J4 Pin 7 north -> Y=49.46 -> U1 Pin 10
p_j4_7 = pad_pos(j4, '7'); p_u1_10 = pad_pos(u1, '10')
add_path([p_j4_7, (p_j4_7[0], 49.46), p_u1_10], nets['/LED_SPK'], pcbnew.F_Cu, 0.2)

# LED_HP: J4 Pin 8 south -> east to X=29.5 -> north to Y=52.00 -> U1 Pin 11
p_j4_8 = pad_pos(j4, '8'); p_u1_11 = pad_pos(u1, '11')
add_path([p_j4_8, (p_j4_8[0], 59.5), (29.5, 59.5), (29.5, 52.00), p_u1_11], nets['/LED_HP'], pcbnew.F_Cu, 0.2)

# Encoder Bus on South corridor:
# Pin 3 (ENC_A: 16.032, 56.0): south on F.Cu to Y=61.0 -> east along Y=61.0 to X=95.0 -> north to U1 Pin 2 (93.62, 57.08)
p_j4_3 = pad_pos(j4, '3'); p_u1_2 = pad_pos(u1, '2')
add_path([p_j4_3, (p_j4_3[0], 61.0), (95.0, 61.0), (95.0, p_u1_2[1]), p_u1_2], nets['/ENC_A'], pcbnew.F_Cu, 0.2)

# Pin 4 (ENC_B: 17.048, 57.78): south on B.Cu to Y=62.0 -> via to F.Cu -> east along Y=62.0 to X=96.3 -> north to U1 Pin 3 (93.62, 54.54)
p_j4_4 = pad_pos(j4, '4'); p_u1_3 = pad_pos(u1, '3')
add_path([p_j4_4, (p_j4_4[0], 62.0)], nets['/ENC_B'], pcbnew.B_Cu, 0.2)
add_via(p_j4_4[0], 62.0, nets['/ENC_B'])
add_path([(p_j4_4[0], 62.0), (96.3, 62.0), (96.3, p_u1_3[1]), p_u1_3], nets['/ENC_B'], pcbnew.F_Cu, 0.2)

# Pin 5 (ENC_SW: 18.064, 56.0): south on B.Cu to Y=63.0 -> via to F.Cu -> east along Y=63.0 to X=97.6 -> north to U1 Pin 4 (93.62, 52.00)
p_j4_5 = pad_pos(j4, '5'); p_u1_4 = pad_pos(u1, '4')
add_path([p_j4_5, (p_j4_5[0], 63.0)], nets['/ENC_SW'], pcbnew.B_Cu, 0.2)
add_via(p_j4_5[0], 63.0, nets['/ENC_SW'])
add_path([(p_j4_5[0], 63.0), (97.6, 63.0), (97.6, p_u1_4[1]), p_u1_4], nets['/ENC_SW'], pcbnew.F_Cu, 0.2)

# ----------------- 6. Ground Infrastructure -----------------
# Connect J4 Pin 1 (DGND) North to DGND zone
p_j4_1 = pad_pos(j4, '1')
add_path([p_j4_1, (p_j4_1[0], 53.0)], nets['DGND'], pcbnew.B_Cu, 0.3)

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# C7 Pad 2 ties south to DGND zone
add_path([p_c7_2, (p_c7_2[0], 37.0)], nets['DGND'], pcbnew.B_Cu, 0.3)

# U2 DGND pins:
# 1. Pad 17 (35.62, 29.62) connects to Pad 4 (28.00, 29.62) across the IC on F.Cu
# 2. Pad 4 connects to adjacent Pad 5 (28.00, 32.16) on F.Cu
# 3. Pad 17 connects East directly into DGND zone at X=49.0 on B.Cu (zero crossings, zero vias!)
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add_path([p_u2_4, p_u2_5], nets['DGND'], pcbnew.F_Cu, 0.3)
add_path([p_u2_17, (49.0, p_u2_17[1])], nets['DGND'], pcbnew.B_Cu, 0.3)

# Note: U2 AGND pins (3, 8, 9, 10, 14) are fully covered and connected by the B.Cu AGND plane.


# ----------------- 7. Zones -----------------
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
